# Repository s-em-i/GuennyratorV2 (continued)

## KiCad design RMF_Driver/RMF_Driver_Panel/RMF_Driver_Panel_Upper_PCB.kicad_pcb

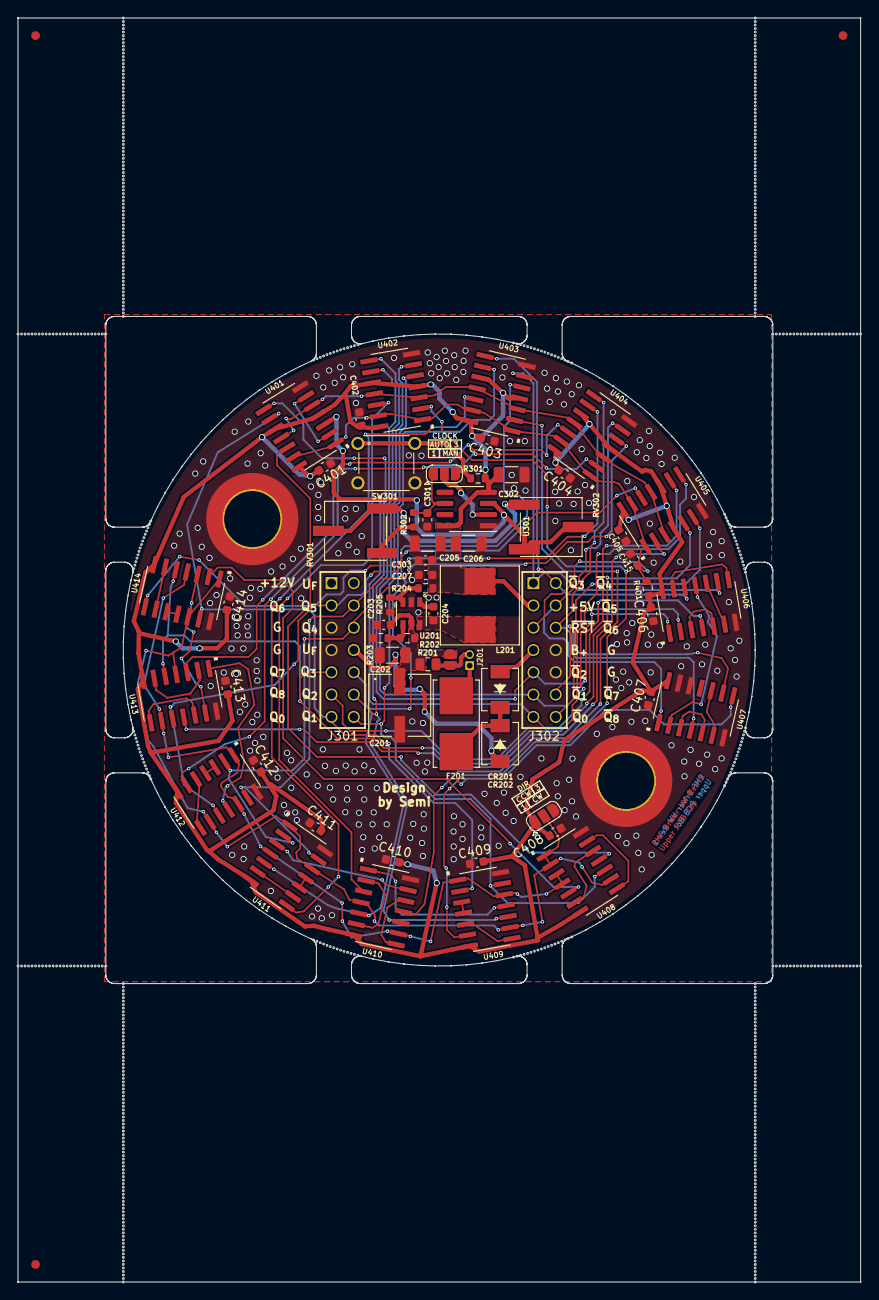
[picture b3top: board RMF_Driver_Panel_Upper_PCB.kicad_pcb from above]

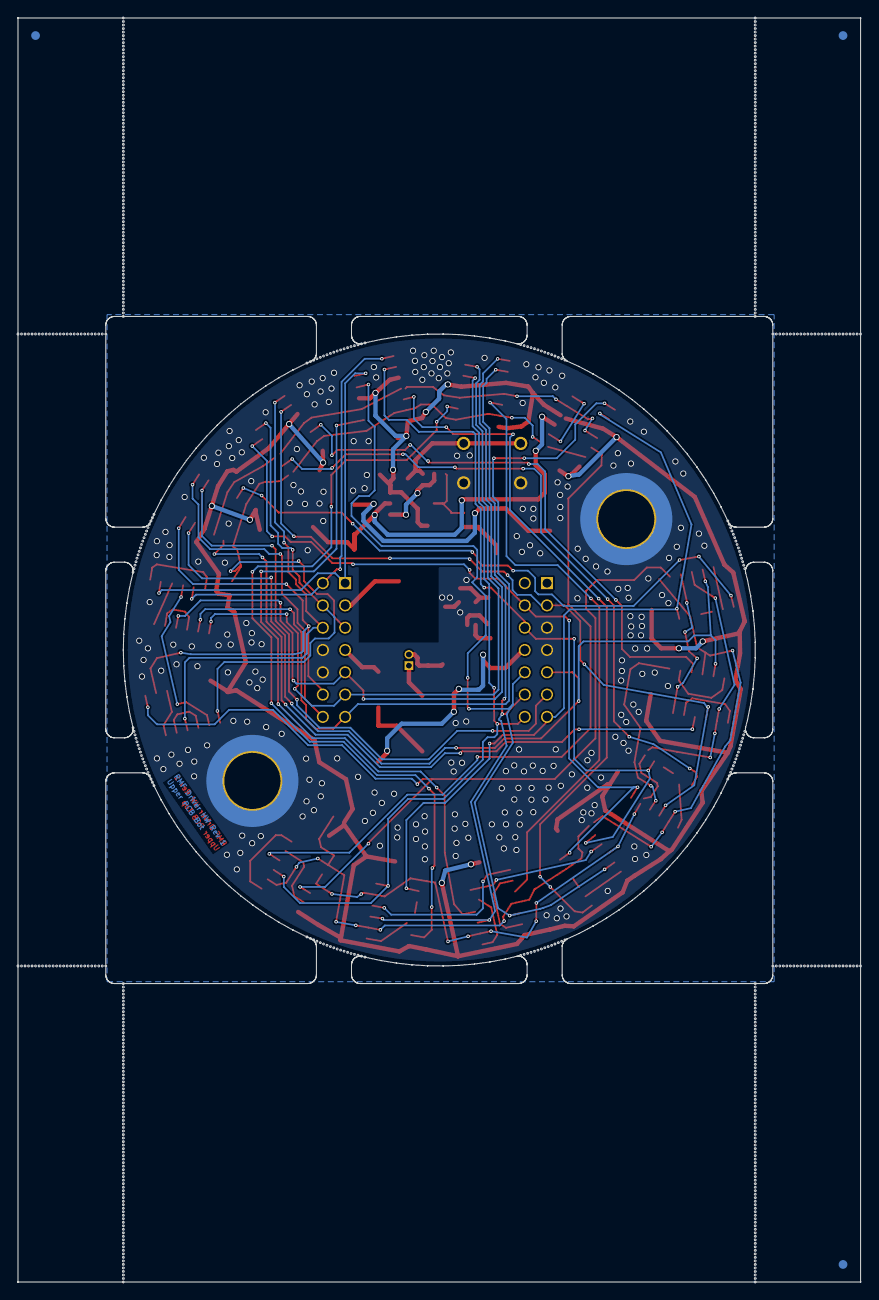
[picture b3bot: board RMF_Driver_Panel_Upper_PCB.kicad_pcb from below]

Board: 2 copper layers, 96.0 x 144.0 mm, 648 parts (3 on the bottom side), 75 nets.

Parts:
C201: 22µ; WCAP-ASLI_865080643008
C202: 2.2µ; C_1206_3216Metric
C203, C204, C207, C303, C401, C402, C403, C404, C405, C406, C407, C408, C409, C410, C411, C412, C413, C414, C415: 100n; C_0603_1608Metric
C205, C206, C302: 22µ; C_1206_3216Metric
C301: 680n; C_0603_1608Metric
CR201, CR202: VS-20BQ030-M3/5BT; VS-20BQ030-M3_5BT
F201: 1.5A T; Fuseholder_Littelfuse_Nano2_154x
H201, H202: MountingHole_Pad; MountingHole_6.4mm_M6_ISO7380_Pad_TopBottom
J201: Conn_02x01; PinHeader_1x02_P1.27mm_Vertical
J301, J302: PinHeader_02x07; SAMTEC_TSW-107-07-G-D
JP201: SolderJumper_2_Open; SolderJumper-2_P1.3mm_Open_RoundedPad1.0x1.5mm
JP301, JP401: SolderJumper_3_Open; SolderJumper-3_P1.3mm_Open_RoundedPad1.0x1.5mm
KiKit_FID_B_1, KiKit_FID_B_2, KiKit_FID_B_3: Fiducial
KiKit_FID_T_1, KiKit_FID_T_2, KiKit_FID_T_3: Fiducial
KiKit_MB_1_4, KiKit_MB_1_5, KiKit_MB_1_6, KiKit_MB_1_7, KiKit_MB_1_8, KiKit_MB_1_9, KiKit_MB_1_10, KiKit_MB_1_11, KiKit_MB_1_12, KiKit_MB_1_13, KiKit_MB_1_14, KiKit_MB_1_15, KiKit_MB_1_16, KiKit_MB_1_17, KiKit_MB_1_18, KiKit_MB_2_4, KiKit_MB_2_5, KiKit_MB_2_6, KiKit_MB_2_7, KiKit_MB_2_8, KiKit_MB_2_9, KiKit_MB_2_10, KiKit_MB_2_11, KiKit_MB_2_12, KiKit_MB_2_13, KiKit_MB_2_14, KiKit_MB_2_15, KiKit_MB_2_16, KiKit_MB_2_17, KiKit_MB_2_18, KiKit_MB_3_2, KiKit_MB_3_3, KiKit_MB_3_4, KiKit_MB_3_5, KiKit_MB_3_6, KiKit_MB_3_7, KiKit_MB_3_8, KiKit_MB_3_9, KiKit_MB_3_10, KiKit_MB_3_11, KiKit_MB_3_12, KiKit_MB_3_13, KiKit_MB_3_14, KiKit_MB_3_15, KiKit_MB_3_16, KiKit_MB_3_17, KiKit_MB_3_18, KiKit_MB_3_19, KiKit_MB_4_3, KiKit_MB_4_4, KiKit_MB_4_5, KiKit_MB_4_6, KiKit_MB_4_7, KiKit_MB_4_8, KiKit_MB_4_9, KiKit_MB_4_10, KiKit_MB_4_11, KiKit_MB_4_12, KiKit_MB_4_13, KiKit_MB_4_14, KiKit_MB_4_15, KiKit_MB_4_16, KiKit_MB_4_17, KiKit_MB_4_18, KiKit_MB_4_19, KiKit_MB_4_20, KiKit_MB_5_5, KiKit_MB_5_6, KiKit_MB_5_7, KiKit_MB_5_8, KiKit_MB_5_9, KiKit_MB_5_10, KiKit_MB_5_11, KiKit_MB_5_12, KiKit_MB_5_13, KiKit_MB_5_14, KiKit_MB_5_15, KiKit_MB_5_16, KiKit_MB_5_17, KiKit_MB_5_18, KiKit_MB_6_2, KiKit_MB_6_3, KiKit_MB_6_4, KiKit_MB_6_5, KiKit_MB_6_6, KiKit_MB_6_7, KiKit_MB_6_8, KiKit_MB_6_9, KiKit_MB_6_10, KiKit_MB_6_11, KiKit_MB_6_12, KiKit_MB_6_13, KiKit_MB_6_14, KiKit_MB_6_15, KiKit_MB_6_16, KiKit_MB_6_17, KiKit_MB_6_18, KiKit_MB_6_19, KiKit_MB_7_4, KiKit_MB_7_5, KiKit_MB_7_6, KiKit_MB_7_7, KiKit_MB_7_8, KiKit_MB_7_9, KiKit_MB_7_10, KiKit_MB_7_11, KiKit_MB_7_12, KiKit_MB_7_13, KiKit_MB_7_14, KiKit_MB_7_15, KiKit_MB_7_16, KiKit_MB_7_17, KiKit_MB_8_3, KiKit_MB_8_4, KiKit_MB_8_5, KiKit_MB_8_6, KiKit_MB_8_7, KiKit_MB_8_8, KiKit_MB_8_9, KiKit_MB_8_10, KiKit_MB_8_11, KiKit_MB_8_12, KiKit_MB_8_13, KiKit_MB_8_14, KiKit_MB_8_15, KiKit_MB_8_16, KiKit_MB_8_17, KiKit_MB_8_18, KiKit_MB_8_19, KiKit_MB_8_20, KiKit_MB_9_6, KiKit_MB_9_7, KiKit_MB_9_8, KiKit_MB_9_9, KiKit_MB_9_10, KiKit_MB_9_11, KiKit_MB_9_12, KiKit_MB_9_13, KiKit_MB_9_14, KiKit_MB_9_15, KiKit_MB_9_16, KiKit_MB_9_17, KiKit_MB_9_18, KiKit_MB_9_19, KiKit_MB_9_20, KiKit_MB_9_21, KiKit_MB_9_22, KiKit_MB_9_23, KiKit_MB_9_24, KiKit_MB_9_25, KiKit_MB_9_26, KiKit_MB_9_27, KiKit_MB_9_28, KiKit_MB_9_29, KiKit_MB_9_30, KiKit_MB_9_31, KiKit_MB_9_32, KiKit_MB_9_33, KiKit_MB_9_34, KiKit_MB_9_35, KiKit_MB_9_36, KiKit_MB_9_37, KiKit_MB_9_38, KiKit_MB_9_39, KiKit_MB_9_40, KiKit_MB_9_41, KiKit_MB_9_42, KiKit_MB_9_43, KiKit_MB_9_44, KiKit_MB_9_45, KiKit_MB_9_46, KiKit_MB_9_47, KiKit_MB_9_48, KiKit_MB_9_49, KiKit_MB_9_50, KiKit_MB_9_51, KiKit_MB_9_52, KiKit_MB_9_53, KiKit_MB_9_54, KiKit_MB_9_55, KiKit_MB_9_56, KiKit_MB_9_57, KiKit_MB_9_58, KiKit_MB_9_59, KiKit_MB_9_60, KiKit_MB_9_61, KiKit_MB_9_62, KiKit_MB_9_63, KiKit_MB_9_64, KiKit_MB_9_65, KiKit_MB_9_66, KiKit_MB_9_67, KiKit_MB_9_68, KiKit_MB_9_69, KiKit_MB_9_70, KiKit_MB_9_71, KiKit_MB_9_72, KiKit_MB_9_73, KiKit_MB_9_74, KiKit_MB_9_75, KiKit_MB_9_76, KiKit_MB_9_77, KiKit_MB_9_78, KiKit_MB_9_79, KiKit_MB_9_80, KiKit_MB_9_81, KiKit_MB_9_82, KiKit_MB_9_83, KiKit_MB_9_84, KiKit_MB_9_85, KiKit_MB_9_86, KiKit_MB_9_87, KiKit_MB_9_88, KiKit_MB_9_89, KiKit_MB_9_90, KiKit_MB_9_91, KiKit_MB_10_6, KiKit_MB_10_7, KiKit_MB_10_8, KiKit_MB_10_9, KiKit_MB_10_10, KiKit_MB_10_11, KiKit_MB_10_12, KiKit_MB_10_13, KiKit_MB_10_14, KiKit_MB_10_15, KiKit_MB_10_16, KiKit_MB_10_17, KiKit_MB_10_18, KiKit_MB_10_19, KiKit_MB_10_20, KiKit_MB_10_21, KiKit_MB_10_22, KiKit_MB_10_23, KiKit_MB_10_24, KiKit_MB_10_25, KiKit_MB_10_26, KiKit_MB_10_27, KiKit_MB_10_28, KiKit_MB_10_29, KiKit_MB_10_30, KiKit_MB_10_31, KiKit_MB_10_32, KiKit_MB_10_33, KiKit_MB_10_34, KiKit_MB_10_35, KiKit_MB_10_36, KiKit_MB_10_37, KiKit_MB_10_38, KiKit_MB_10_39, KiKit_MB_10_40, KiKit_MB_10_41, KiKit_MB_10_42, KiKit_MB_10_43, KiKit_MB_10_44, KiKit_MB_10_45, KiKit_MB_10_46, KiKit_MB_10_47, KiKit_MB_10_48, KiKit_MB_10_49, KiKit_MB_10_50, KiKit_MB_10_51, KiKit_MB_10_52, KiKit_MB_10_53, KiKit_MB_10_54, KiKit_MB_10_55, KiKit_MB_10_56, KiKit_MB_10_57, KiKit_MB_10_58, KiKit_MB_10_59, KiKit_MB_10_60, KiKit_MB_10_61, KiKit_MB_10_62, KiKit_MB_10_63, KiKit_MB_10_64, KiKit_MB_10_65, KiKit_MB_10_66, KiKit_MB_10_67, KiKit_MB_10_68, KiKit_MB_10_69, KiKit_MB_10_70, KiKit_MB_10_71, KiKit_MB_10_72, KiKit_MB_10_73, KiKit_MB_10_74, KiKit_MB_10_75, KiKit_MB_10_76, KiKit_MB_10_77, KiKit_MB_10_78, KiKit_MB_10_79, KiKit_MB_10_80, KiKit_MB_10_81, KiKit_MB_10_82, KiKit_MB_10_83, KiKit_MB_10_84, KiKit_MB_10_85, KiKit_MB_10_86, KiKit_MB_10_87, KiKit_MB_10_88, KiKit_MB_10_89, KiKit_MB_10_90, KiKit_MB_10_91, KiKit_MB_11_6, KiKit_MB_11_7, KiKit_MB_11_8, KiKit_MB_11_9, KiKit_MB_11_10, KiKit_MB_11_11, KiKit_MB_11_12, KiKit_MB_11_13, KiKit_MB_11_14, KiKit_MB_11_15, KiKit_MB_11_16, KiKit_MB_11_17, KiKit_MB_11_18, KiKit_MB_11_19, KiKit_MB_11_20, KiKit_MB_11_21, KiKit_MB_11_22, KiKit_MB_11_23, KiKit_MB_11_24, KiKit_MB_11_25, KiKit_MB_11_26, KiKit_MB_11_27, KiKit_MB_11_28, KiKit_MB_11_29, KiKit_MB_11_30, KiKit_MB_11_31, KiKit_MB_11_32, KiKit_MB_11_33, KiKit_MB_11_34, KiKit_MB_11_35, KiKit_MB_11_36, KiKit_MB_11_37, KiKit_MB_11_38, KiKit_MB_11_39, KiKit_MB_11_40, KiKit_MB_11_41, KiKit_MB_11_42, KiKit_MB_11_43, KiKit_MB_11_44, KiKit_MB_11_45, KiKit_MB_11_46, KiKit_MB_11_47, KiKit_MB_11_48, KiKit_MB_11_49, KiKit_MB_11_50, KiKit_MB_11_51, KiKit_MB_11_52, KiKit_MB_11_53, KiKit_MB_11_54, KiKit_MB_11_55, KiKit_MB_11_56, KiKit_MB_11_57, KiKit_MB_11_58, KiKit_MB_11_59, KiKit_MB_11_60, KiKit_MB_11_61, KiKit_MB_11_62, KiKit_MB_11_63, KiKit_MB_11_64, KiKit_MB_11_65, KiKit_MB_11_66, KiKit_MB_11_67, KiKit_MB_11_68, KiKit_MB_11_69, KiKit_MB_11_70, KiKit_MB_11_71, KiKit_MB_11_72, KiKit_MB_11_73, KiKit_MB_11_74, KiKit_MB_11_75, KiKit_MB_11_76, KiKit_MB_11_77, KiKit_MB_11_78, KiKit_MB_11_79, KiKit_MB_11_80, KiKit_MB_11_81, KiKit_MB_11_82, KiKit_MB_11_83, KiKit_MB_11_84, KiKit_MB_11_85, KiKit_MB_11_86, KiKit_MB_11_87, KiKit_MB_11_88, KiKit_MB_11_89, KiKit_MB_11_90, KiKit_MB_11_91, KiKit_MB_12_6, KiKit_MB_12_7, KiKit_MB_12_8, KiKit_MB_12_9, KiKit_MB_12_10, KiKit_MB_12_11, KiKit_MB_12_12, KiKit_MB_12_13, KiKit_MB_12_14, KiKit_MB_12_15, KiKit_MB_12_16, KiKit_MB_12_17, KiKit_MB_12_18, KiKit_MB_12_19, KiKit_MB_12_20, KiKit_MB_12_21, KiKit_MB_12_22, KiKit_MB_12_23, KiKit_MB_12_24, KiKit_MB_12_25, KiKit_MB_12_26, KiKit_MB_12_27, KiKit_MB_12_28, KiKit_MB_12_29, KiKit_MB_12_30, KiKit_MB_12_31, KiKit_MB_12_32, KiKit_MB_12_33, KiKit_MB_12_34, KiKit_MB_12_35, KiKit_MB_12_36, KiKit_MB_12_37, KiKit_MB_12_38, KiKit_MB_12_39, KiKit_MB_12_40, KiKit_MB_12_41, KiKit_MB_12_42, KiKit_MB_12_43, KiKit_MB_12_44, KiKit_MB_12_45, KiKit_MB_12_46, KiKit_MB_12_47, KiKit_MB_12_48, KiKit_MB_12_49, KiKit_MB_12_50, KiKit_MB_12_51, KiKit_MB_12_52, KiKit_MB_12_53, KiKit_MB_12_54, KiKit_MB_12_55, KiKit_MB_12_56, KiKit_MB_12_57, KiKit_MB_12_58, KiKit_MB_12_59, KiKit_MB_12_60, KiKit_MB_12_61, KiKit_MB_12_62, KiKit_MB_12_63, KiKit_MB_12_64, KiKit_MB_12_65, KiKit_MB_12_66, KiKit_MB_12_67, KiKit_MB_12_68, KiKit_MB_12_69, KiKit_MB_12_70, KiKit_MB_12_71, KiKit_MB_12_72, KiKit_MB_12_73, KiKit_MB_12_74, KiKit_MB_12_75, KiKit_MB_12_76, KiKit_MB_12_77, KiKit_MB_12_78, KiKit_MB_12_79, KiKit_MB_12_80, KiKit_MB_12_81, KiKit_MB_12_82, KiKit_MB_12_83, KiKit_MB_12_84, KiKit_MB_12_85, KiKit_MB_12_86, KiKit_MB_12_87, KiKit_MB_12_88, KiKit_MB_12_89, KiKit_MB_12_90, KiKit_MB_12_91, KiKit_MB_13_6, KiKit_MB_13_7, KiKit_MB_13_8, KiKit_MB_13_9, KiKit_MB_13_10, KiKit_MB_13_11, KiKit_MB_13_12, KiKit_MB_13_13, KiKit_MB_13_14, KiKit_MB_13_15, KiKit_MB_13_16, KiKit_MB_13_17, KiKit_MB_13_18, KiKit_MB_13_19, KiKit_MB_13_20, KiKit_MB_13_21, KiKit_MB_13_22, KiKit_MB_13_23, KiKit_MB_13_24, KiKit_MB_13_25, KiKit_MB_13_26, KiKit_MB_13_27, KiKit_MB_13_28, KiKit_MB_13_29, KiKit_MB_13_30, KiKit_MB_13_31, KiKit_MB_14_6, KiKit_MB_14_7, KiKit_MB_14_8, KiKit_MB_14_9, KiKit_MB_14_10, KiKit_MB_14_11, KiKit_MB_14_12, KiKit_MB_14_13, KiKit_MB_14_14, KiKit_MB_14_15, KiKit_MB_14_16, KiKit_MB_14_17, KiKit_MB_14_18, KiKit_MB_14_19, KiKit_MB_14_20, KiKit_MB_14_21, KiKit_MB_14_22, KiKit_MB_14_23, KiKit_MB_14_24, KiKit_MB_14_25, KiKit_MB_14_26, KiKit_MB_14_27, KiKit_MB_14_28, KiKit_MB_14_29, KiKit_MB_14_30, KiKit_MB_14_31, KiKit_MB_15_6, KiKit_MB_15_7, KiKit_MB_15_8, KiKit_MB_15_9, KiKit_MB_15_10, KiKit_MB_15_11, KiKit_MB_15_12, KiKit_MB_15_13, KiKit_MB_15_14, KiKit_MB_15_15, KiKit_MB_15_16, KiKit_MB_15_17, KiKit_MB_15_18, KiKit_MB_15_19, KiKit_MB_15_20, KiKit_MB_15_21, KiKit_MB_15_22, KiKit_MB_15_23, KiKit_MB_15_24, KiKit_MB_15_25, KiKit_MB_15_26, KiKit_MB_15_27, KiKit_MB_15_28, KiKit_MB_15_29, KiKit_MB_15_30, KiKit_MB_15_31, KiKit_MB_16_6, KiKit_MB_16_7, KiKit_MB_16_8, KiKit_MB_16_9, KiKit_MB_16_10, KiKit_MB_16_11, KiKit_MB_16_12, KiKit_MB_16_13, KiKit_MB_16_14, KiKit_MB_16_15, KiKit_MB_16_16, KiKit_MB_16_17, KiKit_MB_16_18, KiKit_MB_16_19, KiKit_MB_16_20, KiKit_MB_16_21, KiKit_MB_16_22, KiKit_MB_16_23, KiKit_MB_16_24, KiKit_MB_16_25, KiKit_MB_16_26, KiKit_MB_16_27, KiKit_MB_16_28, KiKit_MB_16_29, KiKit_MB_16_30, KiKit_MB_16_31: NPTH
L201: 15µ; WE-LHMI
R201: 5m; R_0805_2012Metric
R202: 768k; R_0603_1608Metric
R203: 200k; R_0603_1608Metric
R204: 88.7k; R_0603_1608Metric
R205: 22.1k; R_0603_1608Metric
R301, R401: 10k; R_0603_1608Metric
R302: 50; R_0603_1608Metric
RV301: 500K; 3361P
RV302: 50K; 3361P
SW301: B3F-1055
U201: PLMR50410XDBVR
U301: TLC555xD; SOIC-8_3.9x4.9mm_P1.27mm
U401, U402, U403, U404, U405: CD74AC74M
U406, U407: CD74AC08M; CD74AC74M
U408, U409, U410, U411, U412, U413, U414: CD74AC00M; CD74AC74M

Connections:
Board_0-+5VA: C205.1, C206.1, C207.1, C302.1, C303.1, C401.1, C402.1, C403.1, C404.1, C405.1, C406.1, C407.1, C408.1, C409.1, C410.1, C411.1, C412.1, C413.1, C414.1, J302.03 (Pin_3), JP401.1 (A), L201.2, R204.1, R301.1, R401.1, U301.4 (R), U301.8 (VCC), U401.4 (~S), U401.10 (~S), U401.14 (VCC), U402.4 (~S), U402.10 (~S), U402.14 (VCC), U403.4 (~S), U403.10 (~S), U403.14 (VCC), U404.4 (~S), U404.10 (~S), U404.14 (VCC), U405.4 (~S), U405.10 (~S), U405.14 (VCC), U406.14 (VCC), U407.14 (VCC), U408.7 (GND), U409.7 (GND), U410.7 (GND), U411.7 (GND), U412.7 (GND), U413.7 (GND), U414.7 (GND)
Board_0-/Power Supply | Temp Sensor/V_{IN}: C201.1, C202.1, C203.1, JP201.2 (B), R201.2, R202.1, U201.5 (VIN)
Board_0-B_{+}^{^}: CR202.2, J302.07 (Pin_7)
Board_0-Clock_{0}: RV302.2, RV302.3, U301.3 (Q), U401.3 (C)
Board_0-Clock_{RSR}: U401.5 (Q), U401.11 (C), U402.3 (C), U402.11 (C), U403.3 (C), U403.11 (C), U404.3 (C), U404.11 (C), U405.3 (C), U405.11 (C)
Board_0-GNDA: C201.2, C202.2, C203.2, C205.2, C206.2, C207.2, C301.2, C302.2, C303.2, C401.2, C402.2, C403.2, C404.2, C405.2, C406.2, C407.2, C408.2, C409.2, C410.2, C411.2, C412.2, C413.2, C414.2, C415.2, H201.1, H202.1, J301.05 (Pin_5), J301.07 (Pin_7), J302.08 (Pin_8), J302.10, JP401.3 (B), R203.2, R205.2, SW301.3, SW301.4, U201.2 (GND), U301.1 (GND), U401.7 (GND), U402.7 (GND), U403.7 (GND), U404.7 (GND), U405.7 (GND), U406.7 (GND), U407.7 (GND), U407.12, U407.13, U408.14 (VCC), U409.14 (VCC), U410.14 (VCC), U411.14 (VCC), U412.14 (VCC), U413.14 (VCC), U414.14 (VCC)
Board_0-Net-(CR201-Pad1): CR201.1, CR202.1, F201.1
Board_0-Net-(JP301-A): C301.1, JP301.1 (A), R302.1, U301.6 (THR)
Board_0-Net-(JP301-B): JP301.3 (B), R301.2, SW301.1, SW301.2
Board_0-Net-(JP301-C): JP301.2 (C), U301.2 (TR)
Board_0-Net-(JP401-C): JP401.2 (C), U408.1, U408.2, U408.9, U409.9, U410.4, U411.1, U411.12, U412.9, U413.4, U414.1, U414.12
Board_0-Net-(R302-Pad2): R302.2, RV301.1
Board_0-Net-(RV301-Pad2): RV301.2, RV301.3, RV302.1
Board_0-Net-(U201-CB): C204.1, U201.1 (CB)
Board_0-Net-(U201-EN): R202.2, R203.1, U201.4 (EN)
Board_0-Net-(U201-FB): R204.2, R205.1, U201.3 (FB)
Board_0-Net-(U201-SW): C204.2, L201.1, U201.6 (SW)
Board_0-Net-(U401A-D): U401.2 (D), U401.6 (~Q)
Board_0-Net-(U401B-D): U401.12 (D), U408.11
Board_0-Net-(U402A-D): U402.2 (D), U409.6
Board_0-Net-(U402B-D): U402.12 (D), U410.3
Board_0-Net-(U403A-D): U403.2 (D), U410.11
Board_0-Net-(U403B-D): U403.12 (D), U411.8
Board_0-Net-(U404A-D): U404.2 (D), U412.6
Board_0-Net-(U404B-D): U404.12 (D), U413.3
Board_0-Net-(U405A-D): U405.2 (D), U413.11
Board_0-Net-(U405B-D): U405.12 (D), U414.8
Board_0-Net-(U406-Pad3): U406.3, U406.5
Board_0-Net-(U406-Pad10): U406.6, U406.10
Board_0-Net-(U406-Pad11): U406.11, U407.2
Board_0-Net-(U406-Pad13): U406.8, U406.13
Board_0-Net-(U407-Pad3): U407.3, U407.5
Board_0-Net-(U407-Pad8): U407.8, U408.5, U414.2
Board_0-Net-(U407-Pad10): U407.6, U407.10
Board_0-Net-(U408-Pad3): U408.3, U408.4, U409.1, U409.12, U410.9, U411.4, U412.1, U412.12, U413.9, U414.4
Board_0-Net-(U408-Pad12): U408.6, U408.12
Board_0-Net-(U408-Pad13): U408.8, U408.13
Board_0-Net-(U409-Pad3): U409.3, U409.4
Board_0-Net-(U409-Pad5): U409.5, U409.8
Board_0-Net-(U409-Pad11): U409.11, U410.1
Board_0-Net-(U410-Pad2): U410.2, U410.6
Board_0-Net-(U410-Pad12): U410.8, U410.12
Board_0-Net-(U410-Pad13): U410.13, U411.3
Board_0-Net-(U411-Pad6): U411.6, U411.9
Board_0-Net-(U411-Pad10): U411.10, U411.11
Board_0-Net-(U412-Pad3): U412.3, U412.4
Board_0-Net-(U412-Pad5): U412.5, U412.8
Board_0-Net-(U412-Pad11): U412.11, U413.1
Board_0-Net-(U413-Pad2): U413.2, U413.6
Board_0-Net-(U413-Pad12): U413.8, U413.12
Board_0-Net-(U413-Pad13): U413.13, U414.3
Board_0-Net-(U414-Pad6): U414.6, U414.9
Board_0-Net-(U414-Pad10): U414.10, U414.11
Board_0-Power_{Off}: J201.2, JP201.1 (A), R201.1
Board_0-Power_{On}: F201.2, J201.1
Board_0-Q_{0}: J301.13, U401.9 (Q), U409.2, U414.13
Board_0-Q_{1}: J301.14, U402.5 (Q), U408.10, U409.13
Board_0-Q_{2}: J301.12, U402.9 (Q), U409.10, U410.10
Board_0-Q_{3}: J301.10, U403.5 (Q), U410.5, U411.5
Board_0-Q_{4}: J301.06 (Pin_6), U403.9 (Q), U411.2, U412.2
Board_0-Q_{5}: J301.04 (Pin_4), U404.5 (Q), U411.13, U412.13
Board_0-Q_{6}: J301.03 (Pin_3), U404.9 (Q), U412.10, U413.10
Board_0-Q_{7}: J301.09 (Pin_9), U405.5 (Q), U413.5, U414.5
Board_0-Q_{8}: J301.11, U405.9 (Q)
Board_0-U_{F}^{^}: CR201.2, J301.08 (Pin_8)
Board_0-~Q_{0}: J302.13, U401.8 (~Q), U406.2
Board_0-~Q_{1}: J302.11, U402.6 (~Q), U406.1
Board_0-~Q_{2}: J302.09 (Pin_9), U402.8 (~Q), U406.4
Board_0-~Q_{3}: J302.01 (Pin_1), U403.6 (~Q), U406.9
Board_0-~Q_{4}: J302.02 (Pin_2), U403.8 (~Q), U406.12
Board_0-~Q_{5}: J302.04 (Pin_4), U404.6 (~Q), U407.1
Board_0-~Q_{6}: J302.06 (Pin_6), U404.8 (~Q), U407.4
Board_0-~Q_{7}: J302.12, U405.6 (~Q), U407.9
Board_0-~Q_{8}: J302.14, U405.8 (~Q)
Board_0-~Reset: C415.1, J302.05 (Pin_5), R401.2, U401.1 (~R), U401.13 (~R), U402.1 (~R), U402.13 (~R), U403.1 (~R), U403.13 (~R), U404.1 (~R), U404.13 (~R), U405.1 (~R), U405.13 (~R)

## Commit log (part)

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2022-05-01 added Johnson Counter Train
2022-05-04 Added 5 Stage Johnsen 1 of 10 Counter
2022-05-05 Added Direction Change Logic
2022-05-06 Added simple Frequency Generator
